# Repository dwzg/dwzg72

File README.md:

dwzg72
======
A simple ATmega32U4 based 72 key ortholinear keyboard made with KiCAD.
Should fit in a 60% keyboard case.

All keys are 1u ortholinear except for:

* split 2u spacebar
* vertical 2u enter key

My personal layout:

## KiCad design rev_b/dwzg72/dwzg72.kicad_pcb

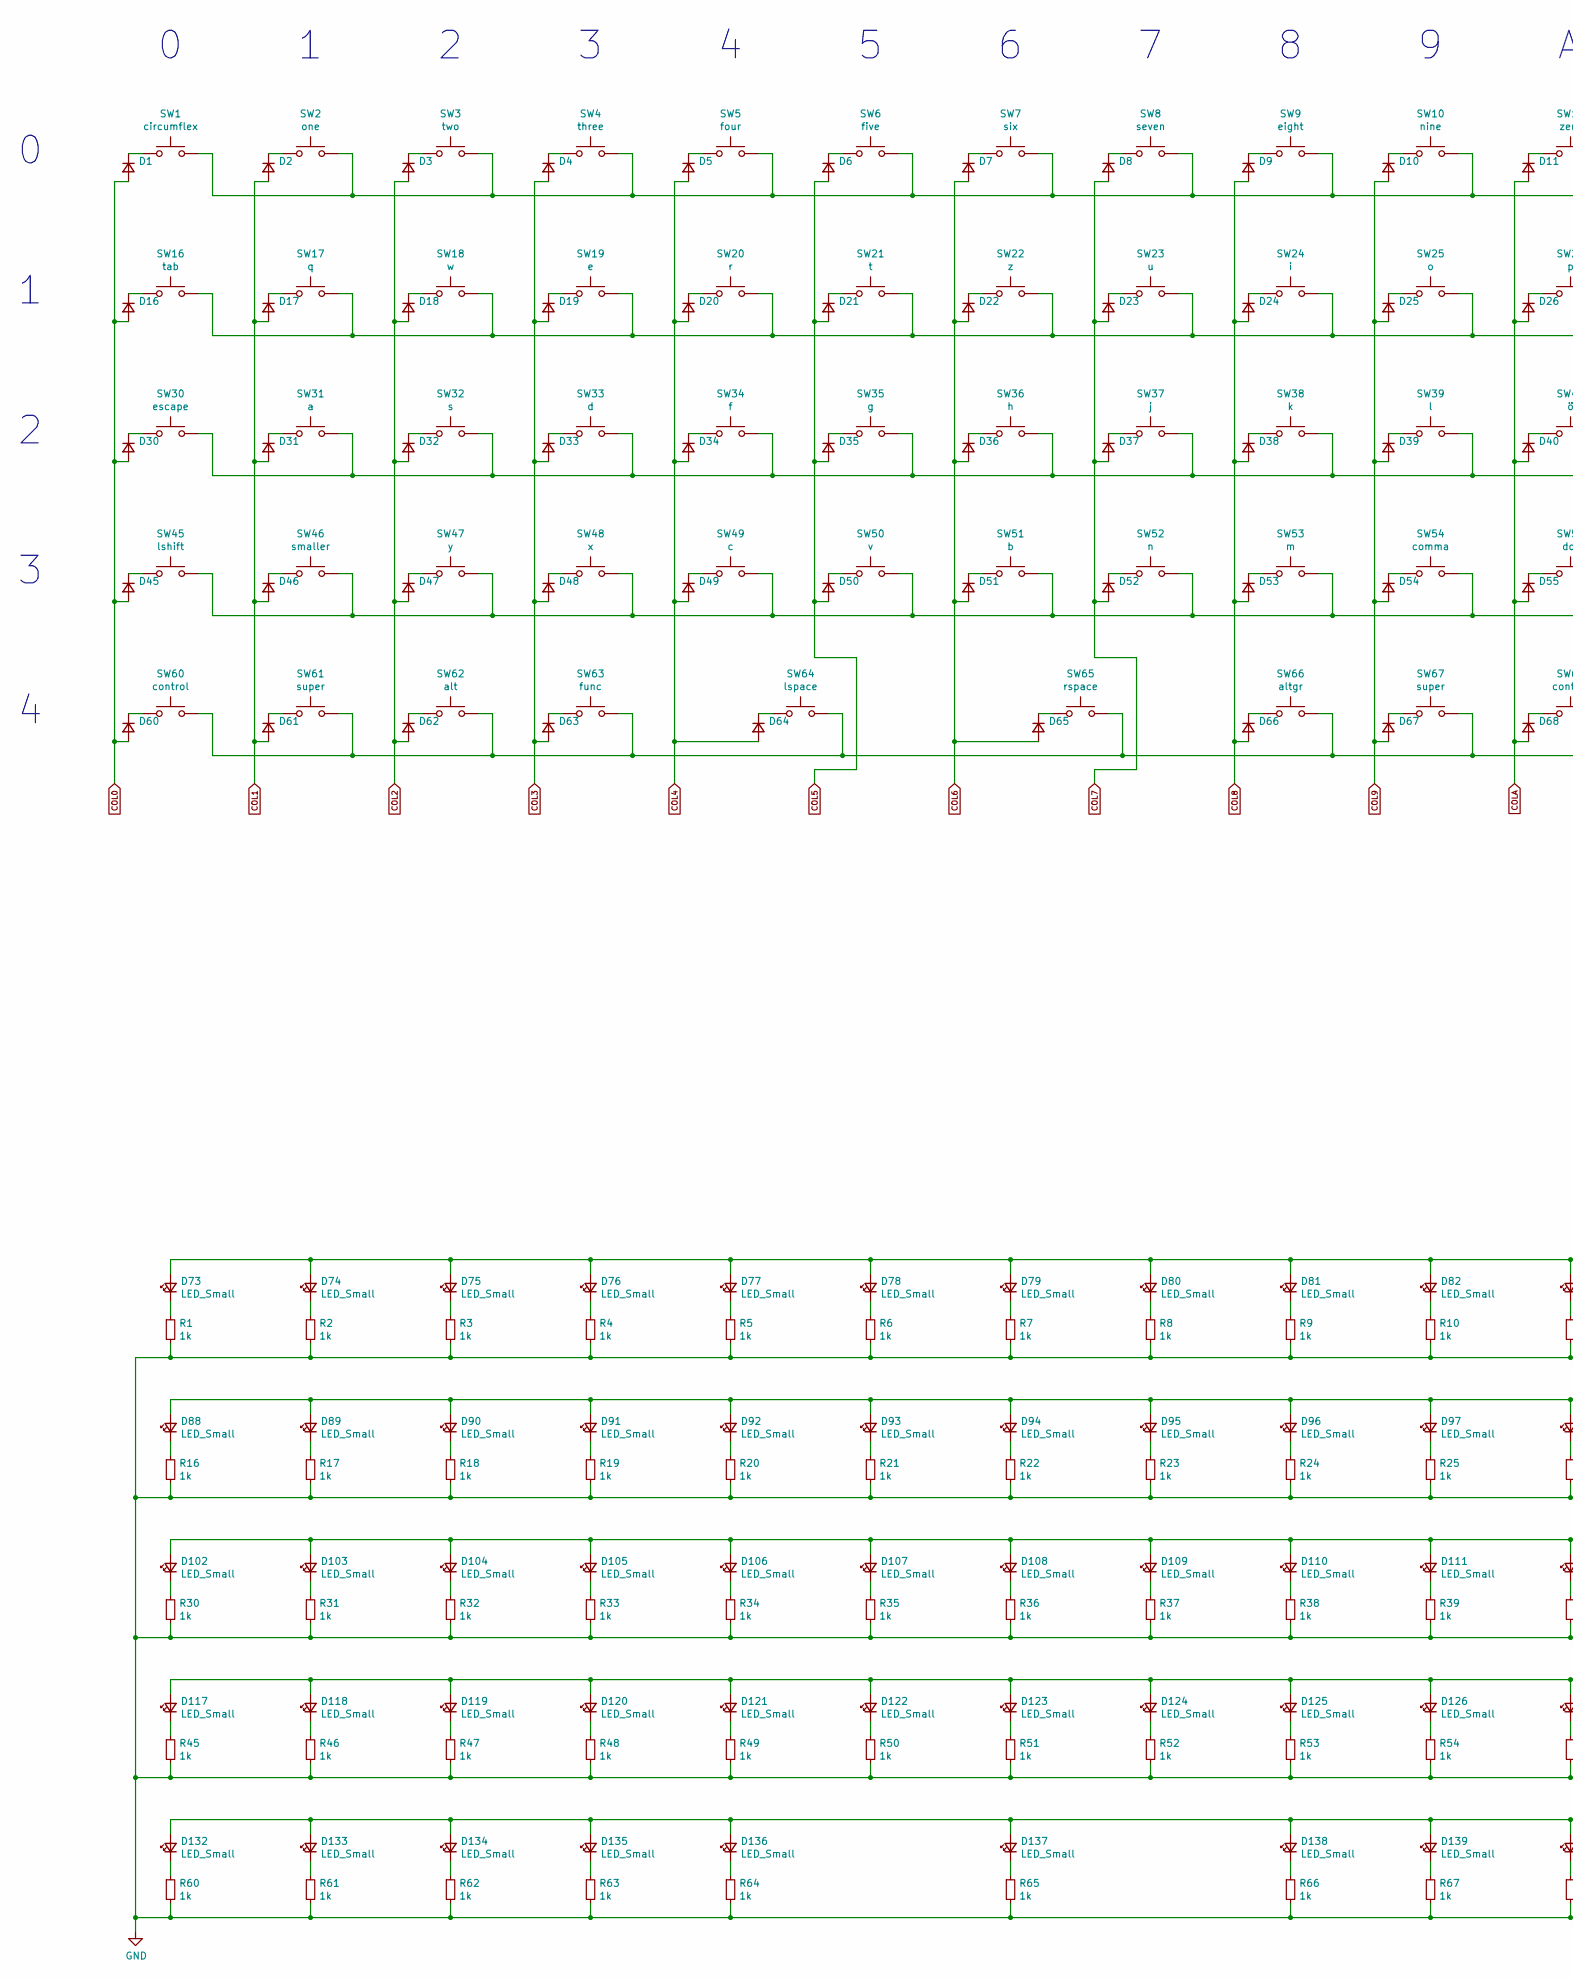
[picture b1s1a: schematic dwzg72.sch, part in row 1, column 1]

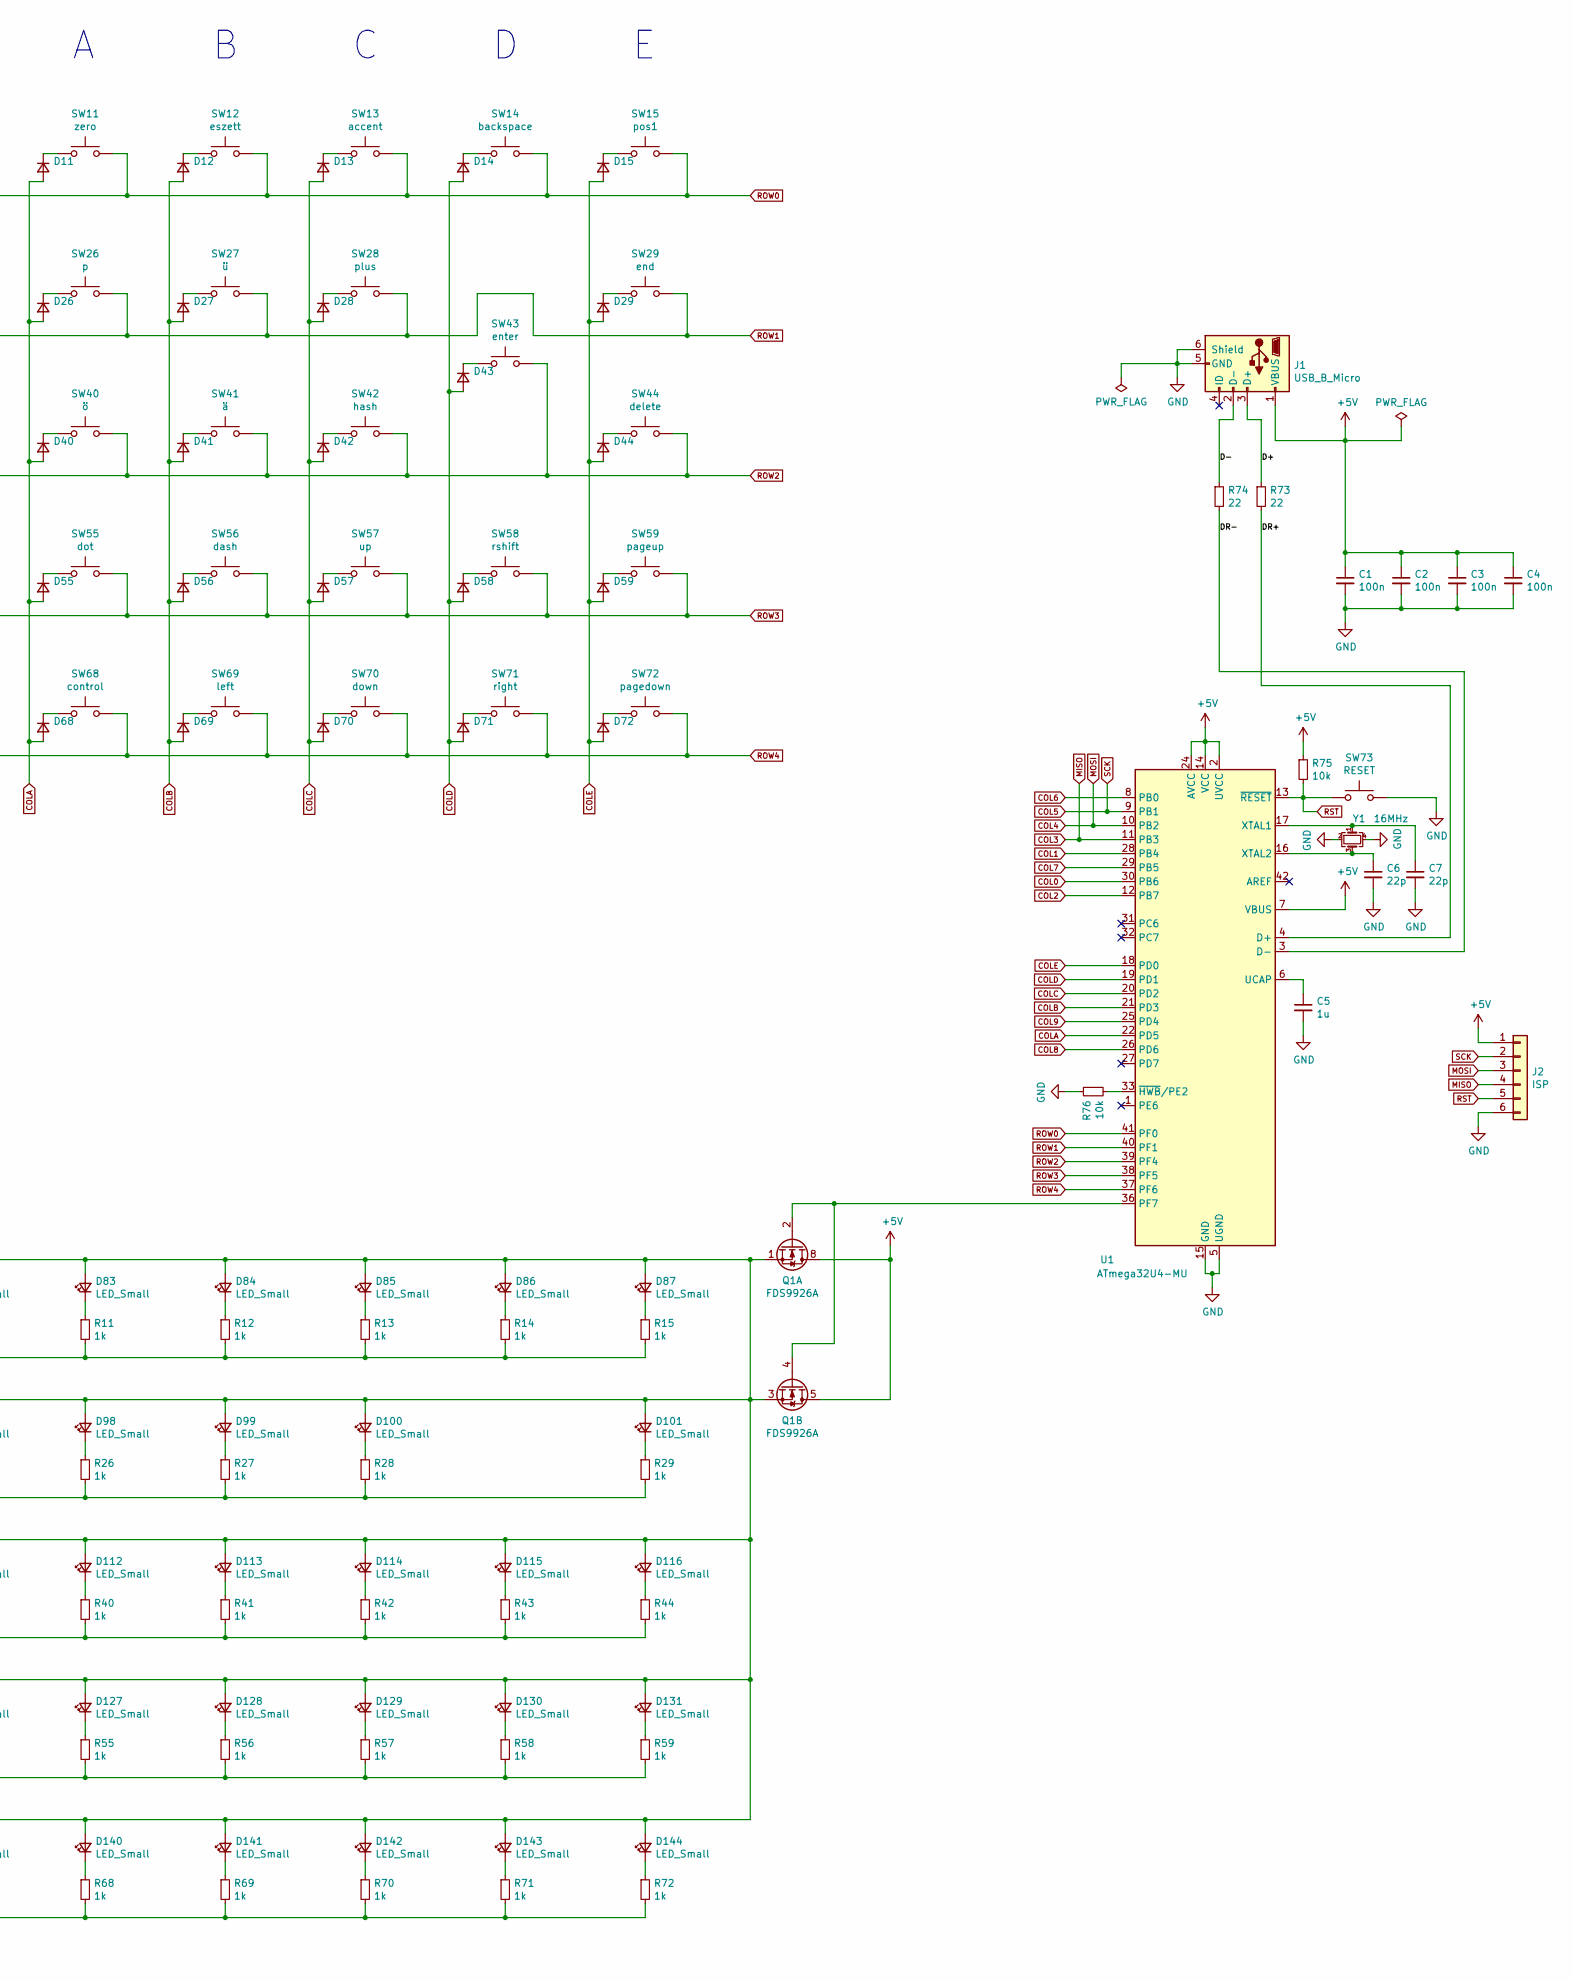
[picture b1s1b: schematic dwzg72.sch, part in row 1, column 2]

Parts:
C1, C2, C3, C4: 100n; C_0603_1608Metric
C5: 1u; C_0603_1608Metric
C6, C7: 22p; C_0603_1608Metric
D1, D2, D3, D4, D5, D6, D7, D8, D9, D10, D11, D12, D13, D14, D15, D16, D17, D18, D19, D20, D21, D22, D23, D24, D25, D26, D27, D28, D29, D30, D31, D32, D33, D34, D35, D36, D37, D38, D39, D40, D41, D42, D43, D44, D45, D46, D47, D48, D49, D50, D51, D52, D53, D54, D55, D56, D57, D58, D59, D60, D61, D62, D63, D64, D65, D66, D67, D68, D69, D70, D71, D72: D_SOD-123F
D73, D74, D75, D76, D77, D78, D79, D80, D81, D82, D83, D84, D85, D86, D87, D88, D89, D90, D91, D92, D93, D94, D95, D96, D97, D98, D99, D100, D101, D102, D103, D104, D105, D106, D107, D108, D109, D110, D111, D112, D113, D114, D115, D116, D117, D118, D119, D120, D121, D122, D123, D124, D125, D126, D127, D128, D129, D130, D131, D132, D133, D134, D135, D136, D137, D138, D139, D140, D141, D142, D143, D144: LED_Small; LED_D3.0mm
J1: USB_B_Micro; USB_Micro-B_Wuerth_629105150521
J2: ISP; PinHeader_1x06_P2.54mm_Vertical
Q1: FDS9926A; SOIC-8_3.9x4.9mm_P1.27mm
R1, R2, R3, R4, R5, R6, R7, R8, R9, R10, R11, R12, R13, R14, R15, R16, R17, R18, R19, R20, R21, R22, R23, R24, R25, R26, R27, R28, R29, R30, R31, R32, R33, R34, R35, R36, R37, R38, R39, R40, R41, R42, R43, R44, R45, R46, R47, R48, R49, R50, R51, R52, R53, R54, R55, R56, R57, R58, R59, R60, R61, R62, R63, R64, R65, R66, R67, R68, R69, R70, R71, R72: 1k; R_0603_1608Metric
R73, R74: 22; R_0603_1608Metric
R75, R76: 10k; R_0603_1608Metric
SW1: circumflex; SW_Cherry_MX_1.00u_PCB
SW2: one; SW_Cherry_MX_1.00u_PCB
SW3: two; SW_Cherry_MX_1.00u_PCB
SW4: three; SW_Cherry_MX_1.00u_PCB
SW5: four; SW_Cherry_MX_1.00u_PCB
SW6: five; SW_Cherry_MX_1.00u_PCB
SW7: six; SW_Cherry_MX_1.00u_PCB
SW8: seven; SW_Cherry_MX_1.00u_PCB
SW9: eight; SW_Cherry_MX_1.00u_PCB
SW10: nine; SW_Cherry_MX_1.00u_PCB
SW11: zero; SW_Cherry_MX_1.00u_PCB
SW12: eszett; SW_Cherry_MX_1.00u_PCB
SW13: accent; SW_Cherry_MX_1.00u_PCB
SW14: backspace; SW_Cherry_MX_1.00u_PCB
SW15: pos1; SW_Cherry_MX_1.00u_PCB
SW16: tab; SW_Cherry_MX_1.00u_PCB
SW17: q; SW_Cherry_MX_1.00u_PCB
SW18: w; SW_Cherry_MX_1.00u_PCB
SW19: e; SW_Cherry_MX_1.00u_PCB
SW20: r; SW_Cherry_MX_1.00u_PCB
SW21: t; SW_Cherry_MX_1.00u_PCB
SW22: z; SW_Cherry_MX_1.00u_PCB
SW23: u; SW_Cherry_MX_1.00u_PCB
SW24: i; SW_Cherry_MX_1.00u_PCB
SW25: o; SW_Cherry_MX_1.00u_PCB
SW26: p; SW_Cherry_MX_1.00u_PCB
SW27: ü; SW_Cherry_MX_1.00u_PCB
SW28: plus; SW_Cherry_MX_1.00u_PCB
SW29: end; SW_Cherry_MX_1.00u_PCB
SW30: escape; SW_Cherry_MX_1.00u_PCB
SW31: a; SW_Cherry_MX_1.00u_PCB
SW32: s; SW_Cherry_MX_1.00u_PCB
SW33: d; SW_Cherry_MX_1.00u_PCB
SW34: f; SW_Cherry_MX_1.00u_PCB
SW35: g; SW_Cherry_MX_1.00u_PCB
SW36: h; SW_Cherry_MX_1.00u_PCB
SW37: j; SW_Cherry_MX_1.00u_PCB
SW38: k; SW_Cherry_MX_1.00u_PCB
SW39: l; SW_Cherry_MX_1.00u_PCB
SW40: ö; SW_Cherry_MX_1.00u_PCB
SW41: ä; SW_Cherry_MX_1.00u_PCB
SW42: hash; SW_Cherry_MX_1.00u_PCB
SW43: enter; SW_Cherry_MX_2.00u_Vertical_PCB
SW44: delete; SW_Cherry_MX_1.00u_PCB
SW45: lshift; SW_Cherry_MX_1.00u_PCB
SW46: smaller; SW_Cherry_MX_1.00u_PCB
SW47: y; SW_Cherry_MX_1.00u_PCB
SW48: x; SW_Cherry_MX_1.00u_PCB
SW49: c; SW_Cherry_MX_1.00u_PCB
SW50: v; SW_Cherry_MX_1.00u_PCB
SW51: b; SW_Cherry_MX_1.00u_PCB
SW52: n; SW_Cherry_MX_1.00u_PCB
SW53: m; SW_Cherry_MX_1.00u_PCB
SW54: comma; SW_Cherry_MX_1.00u_PCB
SW55: dot; SW_Cherry_MX_1.00u_PCB
SW56: dash; SW_Cherry_MX_1.00u_PCB
SW57: up; SW_Cherry_MX_1.00u_PCB
SW58: rshift; SW_Cherry_MX_1.00u_PCB
SW59: pageup; SW_Cherry_MX_1.00u_PCB
SW60, SW68: control; SW_Cherry_MX_1.00u_PCB
SW61, SW67: super; SW_Cherry_MX_1.00u_PCB
SW62: alt; SW_Cherry_MX_1.00u_PCB
SW63: func; SW_Cherry_MX_1.00u_PCB
SW64: lspace; SW_Cherry_MX_2.00u_PCB_Reverse_Stab_Holes
SW65: rspace; SW_Cherry_MX_2.00u_PCB_Reverse_Stab_Holes
SW66: altgr; SW_Cherry_MX_1.00u_PCB
SW69: left; SW_Cherry_MX_1.00u_PCB
SW70: down; SW_Cherry_MX_1.00u_PCB
SW71: right; SW_Cherry_MX_1.00u_PCB
SW72: pagedown; SW_Cherry_MX_1.00u_PCB
SW73: RESET; SW_Push_1P1T_NO_5.1x5.1mm
U1: ATmega32U4-MU; QFN-44-1EP_7x7mm_P0.5mm_EP5.2x5.2mm
Y1: 16MHz; Crystal_SMD_3225-4Pin_3.2x2.5mm

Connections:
+5V: C1.1, C2.1, C3.1, C4.1, J1.1 (VBUS), J2.1, Q1.5 (D2), Q1.6 (D2), Q1.7 (D1), Q1.8 (D1), R75.1, U1.2 (UVCC), U1.7 (VBUS), U1.14 (VCC), U1.24 (AVCC), U1.34 (VCC), U1.44 (AVCC)
/D+: J1.3 (D+), R73.1
/D-: J1.2 (D-), R74.1
/DR+: R73.2, U1.4 (D+)
/DR-: R74.2, U1.3 (D-)
COL0: D1.2 (A), D16.2 (A), D30.2 (A), D45.2 (A), D60.2 (A), U1.30 (PB6)
COL1: D2.2 (A), D17.2 (A), D31.2 (A), D46.2 (A), D61.2 (A), U1.28 (PB4)
COL2: D3.2 (A), D18.2 (A), D32.2 (A), D47.2 (A), D62.2 (A), U1.12 (PB7)
COL3: D4.2 (A), D19.2 (A), D33.2 (A), D48.2 (A), D63.2 (A), J2.4, U1.11 (PB3)
COL4: D5.2 (A), D20.2 (A), D34.2 (A), D49.2 (A), D64.2 (A), J2.3, U1.10 (PB2)
COL5: D6.2 (A), D21.2 (A), D35.2 (A), D50.2 (A), J2.2, U1.9 (PB1)
COL6: D7.2 (A), D22.2 (A), D36.2 (A), D51.2 (A), D65.2 (A), U1.8 (PB0)
COL7: D8.2 (A), D23.2 (A), D37.2 (A), D52.2 (A), U1.29 (PB5)
COL8: D9.2 (A), D24.2 (A), D38.2 (A), D53.2 (A), D66.2 (A), U1.26 (PD6)
COL9: D10.2 (A), D25.2 (A), D39.2 (A), D54.2 (A), D67.2 (A), U1.25 (PD4)
COLA: D11.2 (A), D26.2 (A), D40.2 (A), D55.2 (A), D68.2 (A), U1.22 (PD5)
COLB: D12.2 (A), D27.2 (A), D41.2 (A), D56.2 (A), D69.2 (A), U1.21 (PD3)
COLC: D13.2 (A), D28.2 (A), D42.2 (A), D57.2 (A), D70.2 (A), U1.20 (PD2)
COLD: D14.2 (A), D43.2 (A), D58.2 (A), D71.2 (A), U1.19 (PD1)
COLE: D15.2 (A), D29.2 (A), D44.2 (A), D59.2 (A), D72.2 (A), U1.18 (PD0)
GND: C1.2, C2.2, C3.2, C4.2, C5.2, C6.2, C7.2, J1.5 (GND), J1.6 (Shield), J2.6, R1.2, R2.2, R3.2, R4.2, R5.2, R6.2, R7.2, R8.2, R9.2, R10.2, R11.2, R12.2, R13.2, R14.2, R15.2, R16.2, R17.2, R18.2, R19.2, R20.2, R21.2, R22.2, R23.2, R24.2, R25.2, R26.2, R27.2, R28.2, R29.2, R30.2, R31.2, R32.2, R33.2, R34.2, R35.2, R36.2, R37.2, R38.2, R39.2, R40.2, R41.2, R42.2, R43.2, R44.2, R45.2, R46.2, R47.2, R48.2, R49.2, R50.2, R51.2, R52.2, R53.2, R54.2, R55.2, R56.2, R57.2, R58.2, R59.2, R60.2, R61.2, R62.2, R63.2, R64.2, R65.2, R66.2, R67.2, R68.2, R69.2, R70.2, R71.2, R72.2, R76.1, SW73.2, U1.5 (UGND), U1.15 (GND), U1.23 (GND), U1.35 (GND), U1.43 (GND), U1.45 (GND), Y1.2, Y1.4
unnamed: C5.1, U1.6 (UCAP)
unnamed: C6.1, U1.16 (XTAL2), Y1.3
unnamed: C7.1, U1.17 (XTAL1), Y1.1
unnamed: D1.1 (K), SW1.1
unnamed: D2.1 (K), SW2.1
unnamed: D3.1 (K), SW3.1
unnamed: D4.1 (K), SW4.1
unnamed: D5.1 (K), SW5.1
unnamed: D6.1 (K), SW6.1
unnamed: D7.1 (K), SW7.1
unnamed: D8.1 (K), SW8.1
unnamed: D9.1 (K), SW9.1
unnamed: D10.1 (K), SW10.1
unnamed: D11.1 (K), SW11.1
unnamed: D12.1 (K), SW12.1
unnamed: D13.1 (K), SW13.1
unnamed: D14.1 (K), SW14.1
unnamed: D15.1 (K), SW15.1
unnamed: D16.1 (K), SW16.1
unnamed: D17.1 (K), SW17.1
unnamed: D18.1 (K), SW18.1
unnamed: D19.1 (K), SW19.1
unnamed: D20.1 (K), SW20.1
unnamed: D21.1 (K), SW21.1
unnamed: D22.1 (K), SW22.1
unnamed: D23.1 (K), SW23.1
unnamed: D24.1 (K), SW24.1
unnamed: D25.1 (K), SW25.1
unnamed: D26.1 (K), SW26.1
unnamed: D27.1 (K), SW27.1
unnamed: D28.1 (K), SW28.1
unnamed: D29.1 (K), SW29.1
unnamed: D30.1 (K), SW30.1
unnamed: D31.1 (K), SW31.1
unnamed: D32.1 (K), SW32.1
unnamed: D33.1 (K), SW33.1
unnamed: D34.1 (K), SW34.1
unnamed: D35.1 (K), SW35.1
unnamed: D36.1 (K), SW36.1
unnamed: D37.1 (K), SW37.1
unnamed: D38.1 (K), SW38.1
unnamed: D39.1 (K), SW39.1
unnamed: D40.1 (K), SW40.1
unnamed: D41.1 (K), SW41.1
unnamed: D42.1 (K), SW42.1
unnamed: D43.1 (K), SW43.1
unnamed: D44.1 (K), SW44.1
unnamed: D45.1 (K), SW45.1
unnamed: D46.1 (K), SW46.1
unnamed: D47.1 (K), SW47.1
unnamed: D48.1 (K), SW48.1
unnamed: D49.1 (K), SW49.1
unnamed: D50.1 (K), SW50.1
unnamed: D51.1 (K), SW51.1
unnamed: D52.1 (K), SW52.1
unnamed: D53.1 (K), SW53.1
unnamed: D54.1 (K), SW54.1
unnamed: D55.1 (K), SW55.1
unnamed: D56.1 (K), SW56.1
unnamed: D57.1 (K), SW57.1
unnamed: D58.1 (K), SW58.1
unnamed: D59.1 (K), SW59.1
unnamed: D60.1 (K), SW60.1
unnamed: D61.1 (K), SW61.1
unnamed: D62.1 (K), SW62.1
unnamed: D63.1 (K), SW63.1
unnamed: D64.1 (K), SW64.1
unnamed: D65.1 (K), SW65.1
unnamed: D66.1 (K), SW66.1
unnamed: D67.1 (K), SW67.1
unnamed: D68.1 (K), SW68.1
unnamed: D69.1 (K), SW69.1
unnamed: D70.1 (K), SW70.1
unnamed: D71.1 (K), SW71.1
unnamed: D72.1 (K), SW72.1
unnamed: D73.1 (K), R1.1
unnamed: D74.1 (K), R2.1
unnamed: D75.1 (K), R3.1
unnamed: D76.1 (K), R4.1
unnamed: D77.1 (K), R5.1
unnamed: D78.1 (K), R6.1
unnamed: D79.1 (K), R7.1
unnamed: D80.1 (K), R8.1
unnamed: D81.1 (K), R9.1
unnamed: D82.1 (K), R10.1
unnamed: D83.1 (K), R11.1
unnamed: D84.1 (K), R12.1
unnamed: D85.1 (K), R13.1
unnamed: D86.1 (K), R14.1
unnamed: D87.1 (K), R15.1
unnamed: D88.1 (K), R16.1
unnamed: D89.1 (K), R17.1
unnamed: D90.1 (K), R18.1
unnamed: D91.1 (K), R19.1
unnamed: D92.1 (K), R20.1
unnamed: D93.1 (K), R21.1
unnamed: D94.1 (K), R22.1
unnamed: D95.1 (K), R23.1
unnamed: D96.1 (K), R24.1
unnamed: D97.1 (K), R25.1
unnamed: D98.1 (K), R26.1
unnamed: D99.1 (K), R27.1
unnamed: D100.1 (K), R28.1
unnamed: D73.2 (A), D74.2 (A), D75.2 (A), D76.2 (A), D77.2 (A), D78.2 (A), D79.2 (A), D80.2 (A), D81.2 (A), D82.2 (A), D83.2 (A), D84.2 (A), D85.2 (A), D86.2 (A), D87.2 (A), D88.2 (A), D89.2 (A), D90.2 (A), D91.2 (A), D92.2 (A), D93.2 (A), D94.2 (A), D95.2 (A), D96.2 (A), D97.2 (A), D98.2 (A), D99.2 (A), D100.2 (A), D101.2 (A), D102.2 (A), D103.2 (A), D104.2 (A), D105.2 (A), D106.2 (A), D107.2 (A), D108.2 (A), D109.2 (A), D110.2 (A), D111.2 (A), D112.2 (A), D113.2 (A), D114.2 (A), D115.2 (A), D116.2 (A), D117.2 (A), D118.2 (A), D119.2 (A), D120.2 (A), D121.2 (A), D122.2 (A), D123.2 (A), D124.2 (A), D125.2 (A), D126.2 (A), D127.2 (A), D128.2 (A), D129.2 (A), D130.2 (A), D131.2 (A), D132.2 (A), D133.2 (A), D134.2 (A), D135.2 (A), D136.2 (A), D137.2 (A), D138.2 (A), D139.2 (A), D140.2 (A), D141.2 (A), D142.2 (A), D143.2 (A), D144.2 (A), Q1.1 (S1), Q1.3 (S2)
unnamed: D101.1 (K), R29.1
unnamed: D102.1 (K), R30.1
unnamed: D103.1 (K), R31.1
unnamed: D104.1 (K), R32.1
unnamed: D105.1 (K), R33.1
unnamed: D106.1 (K), R34.1
unnamed: D107.1 (K), R35.1
unnamed: D108.1 (K), R36.1
unnamed: D109.1 (K), R37.1
unnamed: D110.1 (K), R38.1
unnamed: D111.1 (K), R39.1
unnamed: D112.1 (K), R40.1
unnamed: D113.1 (K), R41.1
unnamed: D114.1 (K), R42.1
unnamed: D115.1 (K), R43.1
unnamed: D116.1 (K), R44.1
unnamed: D117.1 (K), R45.1
unnamed: D118.1 (K), R46.1
unnamed: D119.1 (K), R47.1
unnamed: D120.1 (K), R48.1
unnamed: D121.1 (K), R49.1
unnamed: D122.1 (K), R50.1
unnamed: D123.1 (K), R51.1
unnamed: D124.1 (K), R52.1
unnamed: D125.1 (K), R53.1
unnamed: D126.1 (K), R54.1
unnamed: D127.1 (K), R55.1
unnamed: D128.1 (K), R56.1
unnamed: D129.1 (K), R57.1
unnamed: D130.1 (K), R58.1
unnamed: D131.1 (K), R59.1
unnamed: D132.1 (K), R60.1
unnamed: D133.1 (K), R61.1
unnamed: D134.1 (K), R62.1
unnamed: D135.1 (K), R63.1
unnamed: D136.1 (K), R64.1
unnamed: D137.1 (K), R65.1
unnamed: D138.1 (K), R66.1
unnamed: D139.1 (K), R67.1
unnamed: D140.1 (K), R68.1
unnamed: D141.1 (K), R69.1
unnamed: D142.1 (K), R70.1
unnamed: D143.1 (K), R71.1
unnamed: D144.1 (K), R72.1
unnamed: Q1.2 (G1), Q1.4 (G2), U1.36 (PF7)
unnamed: R76.2, U1.33 (~HWB~/PE2)
ROW0: SW1.2, SW2.2, SW3.2, SW4.2, SW5.2, SW6.2, SW7.2, SW8.2, SW9.2, SW10.2, SW11.2, SW12.2, SW13.2, SW14.2, SW15.2, U1.41 (PF0)
ROW1: SW16.2, SW17.2, SW18.2, SW19.2, SW20.2, SW21.2, SW22.2, SW23.2, SW24.2, SW25.2, SW26.2, SW27.2, SW28.2, SW29.2, U1.40 (PF1)
ROW2: SW30.2, SW31.2, SW32.2, SW33.2, SW34.2, SW35.2, SW36.2, SW37.2, SW38.2, SW39.2, SW40.2, SW41.2, SW42.2, SW43.2, SW44.2, U1.39 (PF4)
ROW3: SW45.2, SW46.2, SW47.2, SW48.2, SW49.2, SW50.2, SW51.2, SW52.2, SW53.2, SW54.2, SW55.2, SW56.2, SW57.2, SW58.2, SW59.2, U1.38 (PF5)
ROW4: SW60.2, SW61.2, SW62.2, SW63.2, SW64.2, SW65.2, SW66.2, SW67.2, SW68.2, SW69.2, SW70.2, SW71.2, SW72.2, U1.37 (PF6)
RST: J2.5, R75.2, SW73.1, U1.13 (~RESET)

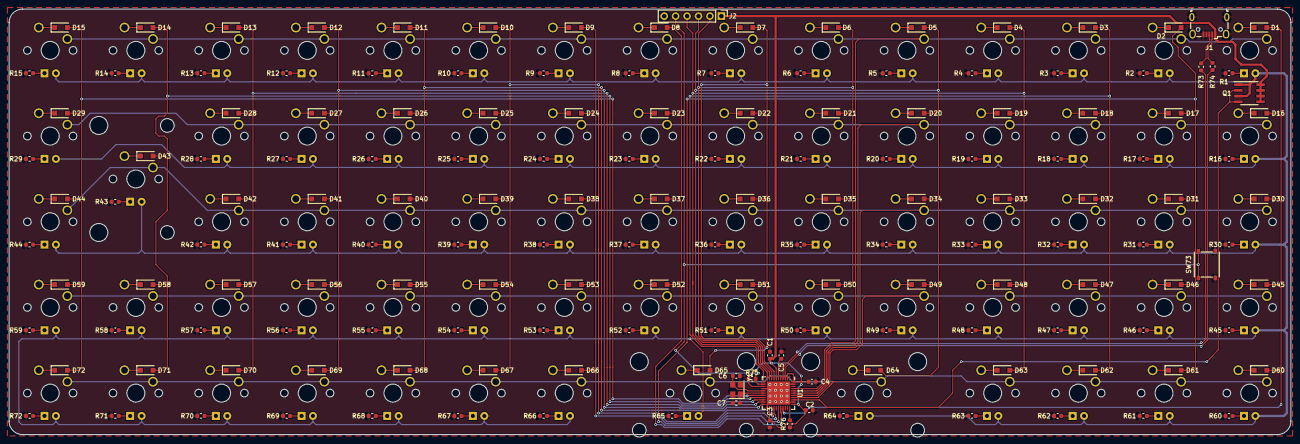
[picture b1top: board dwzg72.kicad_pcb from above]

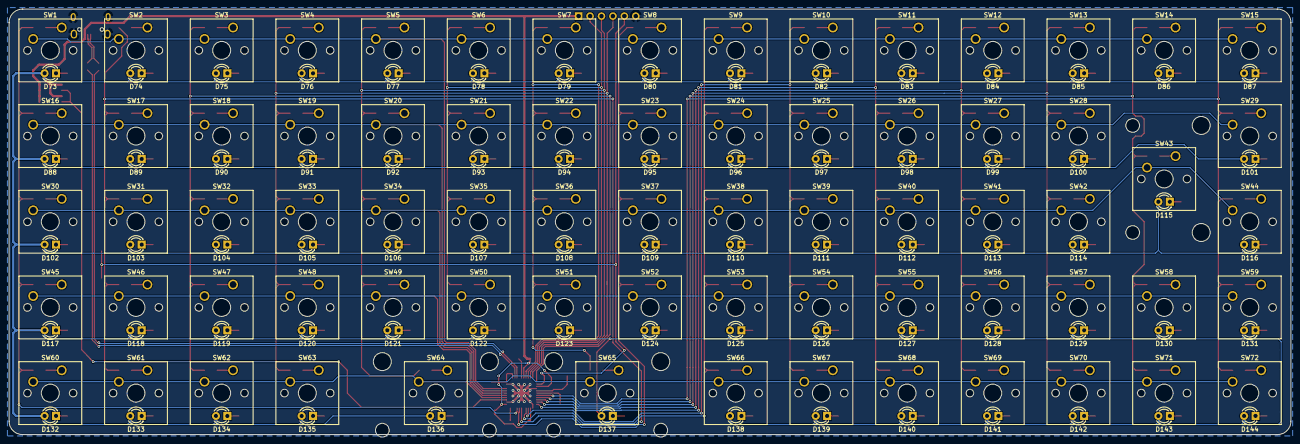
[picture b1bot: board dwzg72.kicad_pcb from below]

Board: 2 copper layers, 285.0 x 94.6 mm, 305 parts (144 on the bottom side), 177 nets.

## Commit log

2020-06-08 Add rev a board
2020-06-08 Update readme and add logo
2020-06-08 Resize logo
2020-06-08 Update readme and rename folder
2020-06-08 Remove unnecessary files
2020-06-08 Add pictures of the PCB
2020-06-12 Add preliminary rev b
2020-06-12 Add logo and revision on PCB
